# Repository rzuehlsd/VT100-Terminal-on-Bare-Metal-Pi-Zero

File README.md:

# PiVT100 Terminal - Enhanced Edition

A VT100 terminal emulator for Raspberry Pi Zero, forked and refactored from PiGFX by Filippo Bergamasco, now rebranded as PiVT100 and enhanced for use with a custom 60% VT100 replica case and adapter board.

## Motivation

Main motivation was that I wanted a terminal emulation for my VT100 replica. Emulation should start within seconds, so a bare metal implementation on a Pi Zero seems to be the way to go. I found the PiGFX implementation by Filippo Bergamasco and used that as a starting point for my modifications. 

Below you see the original VT100 terminal (the color has turned to yellow over the years) and my 60% replica.

If you want a 100% VT100 terminal emulation please go for the VT100 simulation from Lars Brinkhoff (https://github.com/larsbrinkhoff/terminal-simulator)). He simulates the VT100 hardware with original ROMs on a Raspberry Pi. 

## Requirements

My list of requirements was rather short:
- support of VT100 ANSI control sequences, at least of the most important ones
- simulation of a VT100 font and possibly other alternative fonts
- support white on black, amber on black and green on black as terminal font colors
- include simulation of keyclick and bell sound
- configurable via config file at boot and with setup dialog
- design of an adapter board to provide power (Pi and display), RS232 and custom Mini DIN6 connector for UART host connections
- dynamically switch Rx<>Tx to simulate null modem cable
- 8'' display with at least 800x640 pixel resolution (gives about 80x32 chars with VT100 font)
- provide 5VDC power for connected SBCs, like MBC2-Z80

## What's Different from Original PiGFX

The original PiGFX codebase by Filippo Bergamasco has been reduced to the pure VT100 terminal functionality, fully refactored and renamed as PiVT100. Major changes include:

- Removal of graphics, sprites, palette, and font loading features not relevant to VT100 emulation
- Addition of features for VT100 replica hardware integration (switching Rx/Tx, bell, RS232, custom DIN6 connector)
- Improved configuration system and setup dialog
- Consistent naming: main binary is now `pivt100.elf`, config file is `pivt100.txt`, font tools and scripts updated to PiVT100 naming

### Hardware Integration

- **Custom Adapter Board**: PCB design for Raspberry Pi Zero integration into VT100 case
- **Modified Back Cover**: 3D printable back plate designed for 60% VT100 replica case
- **Optimized Pin Layout**: Connector placement adapted for compact VT100 housing

### Software Enhancements

- **Improved Configuration System**: Enhanced `pivt100.txt` file parsing with better error handling
- **Setup Dialog**: Interactive configuration menu accessible via Print Screen key
- **Font Registry**: Multiple built-in fonts with dynamic switching capability
- **Enhanced Keyboard Support**: Better PS/2 keyboard compatibility and layout options
- **Audio Features**: PWM-based bell sound and optional key click feedback
- **Debug System**: Improved logging with configurable verbosity levels

### Configuration Features

- **Runtime Configuration**: Live settings changes through setup dialog
- **Extended Options**: Additional UART, keyboard, and display settings
- **Rx-Tx Switching**: dynamic switching of Tx <> Rx to simulate null modem cable
- **Safe Defaults**: Fallback configuration when SD card config unavailable
- **Layout Support**: Multiple keyboard layouts (US, UK, DE, etc.)

The following picture shows the setup dialog:

<div align="center">
  
</div>

## Hardware Components

### Adapter Board

The custom PCB provides:

- 5VDC / 2A switching power supply for Pi and display
- Raspberry Pi Zero mounting and connections
- PS/2 keyboard connector
- RS232 DB9 connector to interface with host
- Compact form factor for VT100 case integration

Below you see the schematic of the adapter board. The KiCad project is located in directory hardware.

<div align="center">
  
</div>

The following picture shows the prototype of the adapter board still with linear voltage regulator. Final version will hold a switching buck regulator to reduce heat.

<div align="center">
  
</div>

The cable on top of the picture going to the Pi Zero connects the D+/D- pins of the USB connector at the back to two testpoints on the Pi. This allows the usage of a standard USB keyboard to be connected to the Pi Zero without additional adapter. For more details please see https://maker-tutorials.com/raspberry-pi-zero-mit-usb-buchse-typ-a-erweitern-anloeten/.

As it's very hard to find a real RS232 null modem cable, the signal relay (blue) is used to switch the Rx and Tx lines to simulate a null modem cable, if required.
The resistors between Pi Zero and relay are used to level shift the RxD signal (only signal that goes into the Pi) to voltage levels below 3.3V.
The connectors on the back besides the USB-A are a Mini DIN6 connector (for a custom connection to an MBC2-Z80), an RS232 connector module and a 5.5mm power connector.

More information is given in directory hardware.

### Modified Back Cover

The 3D printable back plate features:

- Mounting points for Raspberry Pi Zero adapter board
- Cutouts for power, UART connections and SD card extension cable
- Compatible with 60% VT100 replica cases

This back cover fits into the opening at the back of the VT100 case and has supports to connect the PCB (holes have to be drilled manually to allow for small adjustments). There is also a support to hold the SD card extension to allow changing the SD card at the back of the case. The other openings fit the connectors on the adapter board and allow mounting of a small ON/OFF switch.

<div align="center">
  
</div>

## Quick Setup

### Hardware Assembly

1. Populate the adapter board starting with the smallest components
2. Check installed submodules (e.g. power supply, connectors, etc.)
3. Install Raspberry Pi Zero on adapter board
4. Mount assembly in VT100 case with modified back cover
5. Connect PS/2 keyboard to adapter board
6. Connect power supply

## Assembly of VT100 replica case

The case was printed on a Bamboo Lab P1S printer using the STL-files provided by megardi. I discovered that the different parts which have to be glued together did not always fit very well. So be prepared to use a lot of filler and do a lot of sanding. It took some time but in the end the result was quite good. I used a special filler for plastics to prepare for the final painting. I discovered that the original color of the VT100 was "oyster white" and by comparing a RAL color table with a picture of the inside of a real VT100 I found that RAL 1013 fits very well.

Here are some pictures of the assembly process:

<div align="center">

</div>

I used a simple 8'' display from Aliexpress with 1024x768 pixels. The display had no brightness regulation (neither per HDMI nor external). For the future I would recommend using a controller with brightness control, if possible through software.

In the pictures above I used the resolution 800x640 pixel. With 1024x768 the first 2 characters are covered by the screen bezel. 

To connect the display to the Pi Zero I used a flexible adapter cable miniHDMI to miniHDMI (C1-C1). I also installed an SD Card extension cable for easy access to the SD card slot at the back of the case.

Display:        https://de.aliexpress.com/item/1005004162403387.html?spm=a2g0o.order_list.order_list_main.64.759e5c5fCtHg3D&gatewayAdapt=glo2deu
Cable:          https://de.aliexpress.com/item/1005008622570470.html?spm=a2g0o.order_list.order_list_main.59.7f095c5f7ZEnkL&gatewayAdapt=glo2deu
SD Card Extension:  https://de.aliexpress.com/item/4001200431510.html?spm=a2g0o.order_list.order_list_main.87.759e5c5fCtHg3D&gatewayAdapt=glo2deu

### Software Installation

1. Format SD card as FAT32
2. Copy `bootcode.bin`, `start.elf`, `kernel.img` and `pivt100.txt` to SD card root
3. Insert SD card and power on
4. Connect UART at 115200 baud for terminal access
5. Adjust terminal settings via setup dialog to your needs

### Configuration

- **Interactive Setup**: Press Print Screen key when the keyboard is connected
- **File Configuration**: Edit `pivt100.txt` on SD card for persistent settings
- **Default Settings**: System works out-of-box with reasonable defaults

## Basic Configuration (`pivt100.txt`)

```ini
# Display Settings
displayWidth = 1024
displayHeight = 768
fontSelection = 2
foregroundColor = 10
backgroundColor = 0

# UART Settings
baudrate = 115200
switchRxTx = 0

# Keyboard Settings
keyboardLayout = us
useUsbKeyboard = 1
keyboardAutorepeat = 1

# Audio Settings
soundLevel = 50
keyClick = 1
```

## Building from Source

```bash
# Build for Raspberry Pi Zero
make RPI=1

# Clean build
make clean
```

## Known Issues

### Display Frame Coverage

- **1024x768 Resolution**: First two characters may be covered by screen bezel
- **Workaround**: Avoid critical text in leftmost positions
- **Future Fix**: Logical screen offset implementation planned

## Hardware Files

- **PCB Design**: Located in `/hardware` directory (KiCad format)
- **3D Models**: OpenSCAD files for back cover modifications in `/OpenScad`
- **Assembly Guide**: See `/doc` for detailed assembly instructions

## Project History

This project is a fork and full refactor of [PiGFX](https://github.com/fbergama/pigfx) by Filippo Bergamasco. All code, configuration, and documentation have been updated to use the PiVT100 name and structure. The original project provided the core VT100 terminal emulation and graphics capabilities.

VT100 replica in 60% size was designed by megardi (https://www.instructables.com/23-Scale-VT100-Terminal-Reproduction/).

## License

Copyright (C) 2014-2020 Filippo Bergamasco (Original PiGFX)
Copyright (C) 2025 Ralf Zühlsdorff (PiVT100 Edition)

Licensed under the MIT License - see LICENSE file for details.

## Contributing

Contributions welcome for:

- Hardware design improvements
- Software feature enhancements  
- Documentation updates
- Testing on different Pi models

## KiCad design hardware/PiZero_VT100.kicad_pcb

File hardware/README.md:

# Carrier Board for Pi Zero VT100 Terminal
<div align="center">
RZ 9/2015
</br>
</br>
</div>

This project designs and builds a carrier board for the Raspberry Pi Zero that, together with the pigfx_V20 software, enables a bare‑metal implementation of a VT100 terminal.

The software features are described in the directory PIGFX_20, including the enhancements over the original version. This software version extends the PiGFX project by Filippo Bergamasco.

The carrier board can be mounted directly in the rear panel of a terminal enclosure and provides the following components:
- 5 VDC / 2 A power supply (input 7–9 V DC or AC / 2 A wall adapter)
- RS‑232 interface to the host computer
- Alternative host interface via Mini‑DIN‑6 connector and 4‑pin header
- USB‑A connector for a wired USB keyboard
- Switch (relay) to swap RxD and TxD
- 800 Hz buzzer (optional)

The Pi Zero GPIO pins are not 5 V tolerant. Therefore, all incoming signals (here: RxD only) must be level‑shifted from 5 V to 3.3 V. Outgoing signals are 5 V‑level compatible for typical systems.

The RxD level shifting is implemented with a resistor divider: 820 Ω and 1.5 kΩ. No issues have been observed even at 115200 baud.

The updated version was prototyped on the old PCB. The 74HC5040 was desoldered and the RxD signal was routed to the Pi through the resistor divider. All other signals were wired directly to the Pi Zero with jumpers.

Testing also showed that the 7805 linear regulator needs a small heatsink for stable operation. On the old board, a small heatsink was provisionally installed for testing. With the heatsink, the 7805 ran stably and supplied power not only to the Pi Zero but also to the MSBC2‑Z80 running CP/M. 

In the final version, the LCD display must also be supplied from the 5 V rail with about 1 A. Therefore, the 5 V supply must provide at least 2 A and use a larger heatsink with about 6 K/W thermal resistance. Therefore the 7805 was replaced by a LM350 regulator, which can provided up to 3A with proper heatsink.

All changes have been reflected in the schematic and layout.

An adapter for the MBC2‑Z80 to connect the Z80 via the Mini‑DIN‑8 connector is described in the sub‑project “Z80‑SBC_Adapter”.

Board revisions:
- [x] Barrel jack for 9 V DC / AC input
- [x] Replace regulator with LM350
- [x] Check heatsink and install a larger one if needed
- [x] LED indicator On/Off
- [x] Contacts for power switch
- [x] RxD <> TxD swap via relay, switchable by Pi GPIO pin
- [x] USB‑A socket for keyboard connection
- [x] Mini‑DIN‑6 socket for direct MBC2 connection with power
- [x] RS‑232 DB9 connector
- [x] Internal header for direct MBC2 connection inside the terminal enclosure
- [x] PCB cut‑out for the USB plug (very short pins)
- [x] Buzzer / speaker circuit added
    - [x] Pads for piezo buzzer, 12.5 mm diameter, 5 mm pitch
- [x] Schematic revised for external fabrication

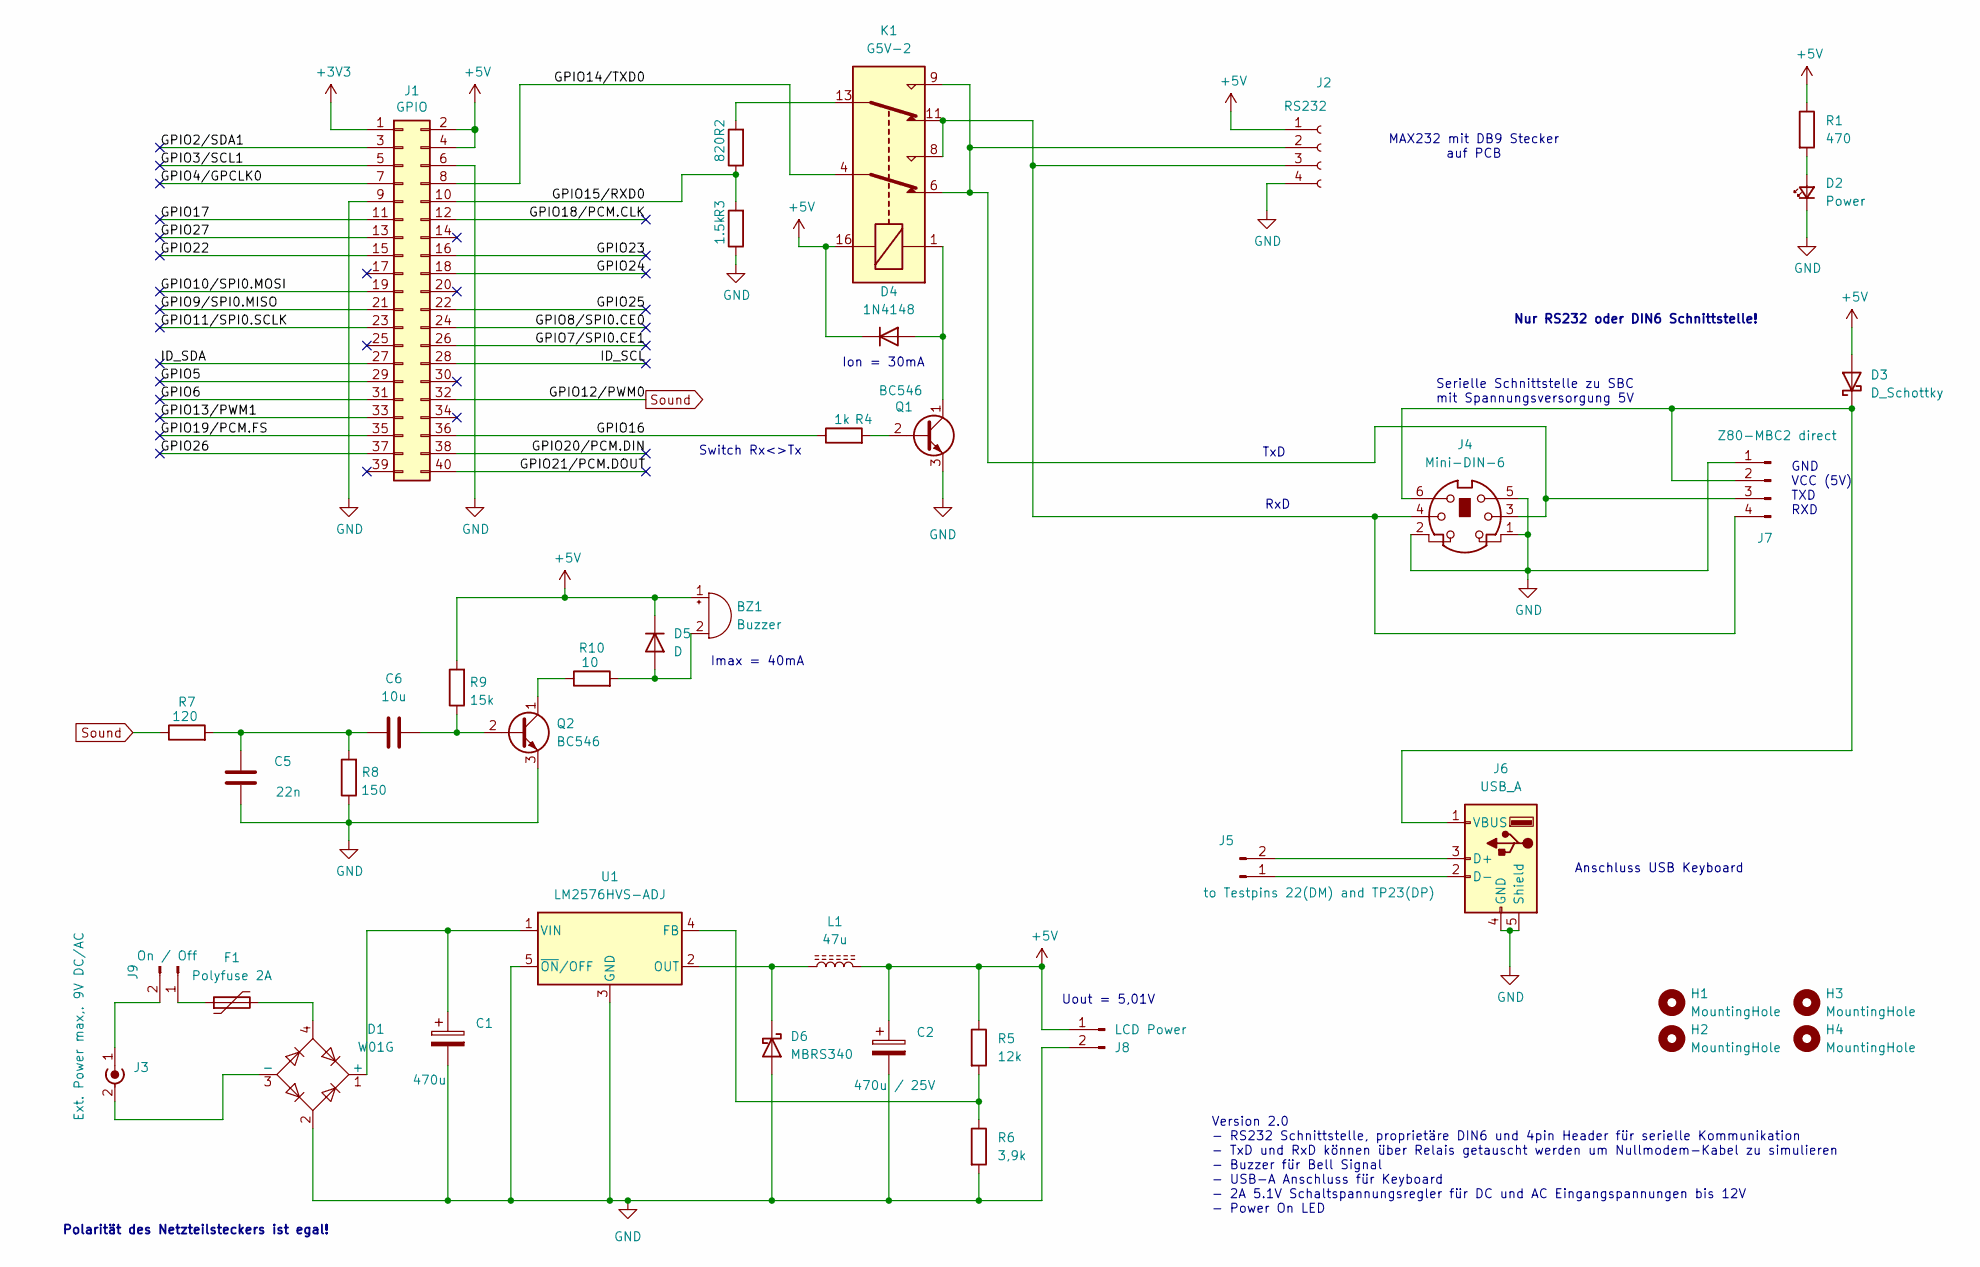
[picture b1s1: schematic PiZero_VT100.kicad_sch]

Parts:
BZ1: Buzzer; MagneticBuzzer_ProSignal_ABI-009-RC
C1: 470u; CP_Elec_10x10
C2: 470u / 25V; CP_Elec_10x10
C5: 22n; C_Rect_L7.0mm_W4.5mm_P5.00mm
C6: 10u; C_Rect_L9.0mm_W2.6mm_P7.50mm_MKT
D1: W01G; Diode_Bridge_Round_D9.8mm
D2: Power; LED_D3.0mm
D3: D_Schottky; D_DO-15_P12.70mm_Horizontal
D4: 1N4148; D_A-405_P10.16mm_Horizontal
D5: D; D_A-405_P10.16mm_Horizontal
D6: MBRS340; D_SMC
F1: Polyfuse 2A; Fuse_Littelfuse-LVR200
H1, H2, H3, H4: MountingHole; MountingHole_3.2mm_M3
J1: GPIO; PinSocket_2x20_P2.54mm_Vertical
J2: RS232; PinSocket_1x04_P2.54mm_Vertical
J3: Ext. Power max,. 9V DC/AC; BarrelJack_GCT_DCJ200-10-A_Horizontal
J4: Mini-DIN-6; J_Mini-DIN-6
J5: to Testpins 22(DM) and TP23(DP); PinHeader_1x02_P2.54mm_Vertical
J6: USB_A; USB_A_Stewart_SS-52100-001_Horizontal
J7: Z80-MBC2 direct; PinHeader_1x04_P2.54mm_Vertical
J8: LCD Power; PinHeader_1x02_P2.54mm_Vertical
J9: On / Off; PinHeader_1x02_P2.54mm_Vertical
K1: G5V-2; Relay_DPDT_Omron_G5V-2
L1: 47u; L_Fastron_PISN
Q1, Q2: BC546; TO-92_Wide
R1: 470; R_Axial_DIN0207_L6.3mm_D2.5mm_P10.16mm_Horizontal
R2: 820; R_Axial_DIN0207_L6.3mm_D2.5mm_P10.16mm_Horizontal
R3: 1.5k; R_Axial_DIN0207_L6.3mm_D2.5mm_P10.16mm_Horizontal
R4: 1k; R_Axial_DIN0207_L6.3mm_D2.5mm_P10.16mm_Horizontal
R5: 12k; R_1206_3216Metric_Pad1.30x1.75mm_HandSolder
R6: 3,9k; R_1206_3216Metric_Pad1.30x1.75mm_HandSolder
R7: 120; R_Axial_DIN0207_L6.3mm_D2.5mm_P10.16mm_Horizontal
R8: 150; R_Axial_DIN0207_L6.3mm_D2.5mm_P10.16mm_Horizontal
R9: 15k; R_Axial_DIN0207_L6.3mm_D2.5mm_P10.16mm_Horizontal
R10: 10; R_Axial_DIN0207_L6.3mm_D2.5mm_P10.16mm_Horizontal
U1: LM2576HVS-ADJ; TO-263-5_TabPin3

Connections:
+3V3: J1.1
+5V: BZ1.1 (+), C2.1, D3.2 (A), D4.1 (K), D5.1 (K), J1.2, J1.4, J2.1, J8.1, K1.16, L1.2, R1.1, R5.1, R9.2
/GPIO2/SDA1: J1.3
/GPIO3/SCL1: J1.5
/GPIO4/GPCLK0: J1.7
/GPIO5: J1.29
/GPIO6: J1.31
/GPIO7/SPI0.CE1: J1.26
/GPIO8/SPI0.CE0: J1.24
/GPIO9/SPI0.MISO: J1.21
/GPIO10/SPI0.MOSI: J1.19
/GPIO11/SPI0.SCLK: J1.23
/GPIO13/PWM1: J1.33
/GPIO14/TXD0: J1.8, K1.4
/GPIO15/RXD0: J1.10, R2.1, R3.2
/GPIO16: J1.36, R4.1
/GPIO17: J1.11
/GPIO18/PCM.CLK: J1.12
/GPIO19/PCM.FS: J1.35
/GPIO20/PCM.DIN: J1.38
/GPIO21/PCM.DOUT: J1.40
/GPIO22: J1.15
/GPIO23: J1.16
/GPIO24: J1.18
/GPIO25: J1.22
/GPIO26: J1.37
/GPIO27: J1.13
/ID_SCL: J1.28
/ID_SDA: J1.27
GND: C1.2, C2.2, C5.2, D1.2, D2.1 (K), D6.2 (A), J1.6, J1.9, J2.4, J4.1, J4.2, J4.5, J6.4 (GND), J6.5 (Shield), J7.1, J8.2, Q1.3 (E), Q2.3 (E), R3.1, R6.2, R8.1, U1.3 (GND), U1.5 (~ON/OFF)
unnamed: BZ1.2 (-), D5.2 (A), R10.2
unnamed: C5.1, C6.1, R7.2, R8.2
unnamed: C1.1, D1.1 (+), U1.1 (VIN)
unnamed: D1.3 (-), J3.2 (Ext)
unnamed: D1.4, F1.2
unnamed: D2.2 (A), R1.2
unnamed: D3.1 (K), J4.6, J6.1 (VBUS), J7.2
unnamed: D4.2 (A), K1.1, Q1.1 (C)
unnamed: D6.1 (K), L1.1, U1.2 (OUT)
unnamed: J2.2, J4.3, J7.3, K1.6, K1.9
unnamed: J2.3, J4.4, J7.4, K1.8, K1.11
unnamed: J3.1 (In), J9.2
unnamed: J5.1, J6.2 (D-)
unnamed: J5.2, J6.3 (D+)
unnamed: F1.1, J9.1
unnamed: K1.13, R2.2
unnamed: Q1.2 (B), R4.2
unnamed: C6.2, Q2.2 (B), R9.1
unnamed: Q2.1 (C), R10.1
unnamed: R5.2, R6.1, U1.4 (FB)
Sound: J1.32, R7.1

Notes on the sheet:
Imax = 40mA
TxD
RxD
Version 2.0 - RS232 Schnittstelle, proprietäre DIN6 und 4pin Header für serielle Kommunikation - TxD und RxD können über Relais getauscht werden um Nullmodem-Kabel zu simulieren - Buzzer für Bell Signal - USB-A Anschluss für Keyboard - 2A 5.1V Schaltspannungsregler für DC und AC Eingangspannungen b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
Ion = 30mA
MAX232 mit DB9 Stecker auf PCB
Anschluss USB Keyboard
Nur RS232 oder DIN6 Schnittstelle!
Serielle Schnittstelle zu SBC mit Spannungsversorgung 5V
Switch Rx<>Tx
GND VCC (5V) TXD RXD
Uout = 5,01V
Polarität des Netzteilsteckers ist egal!

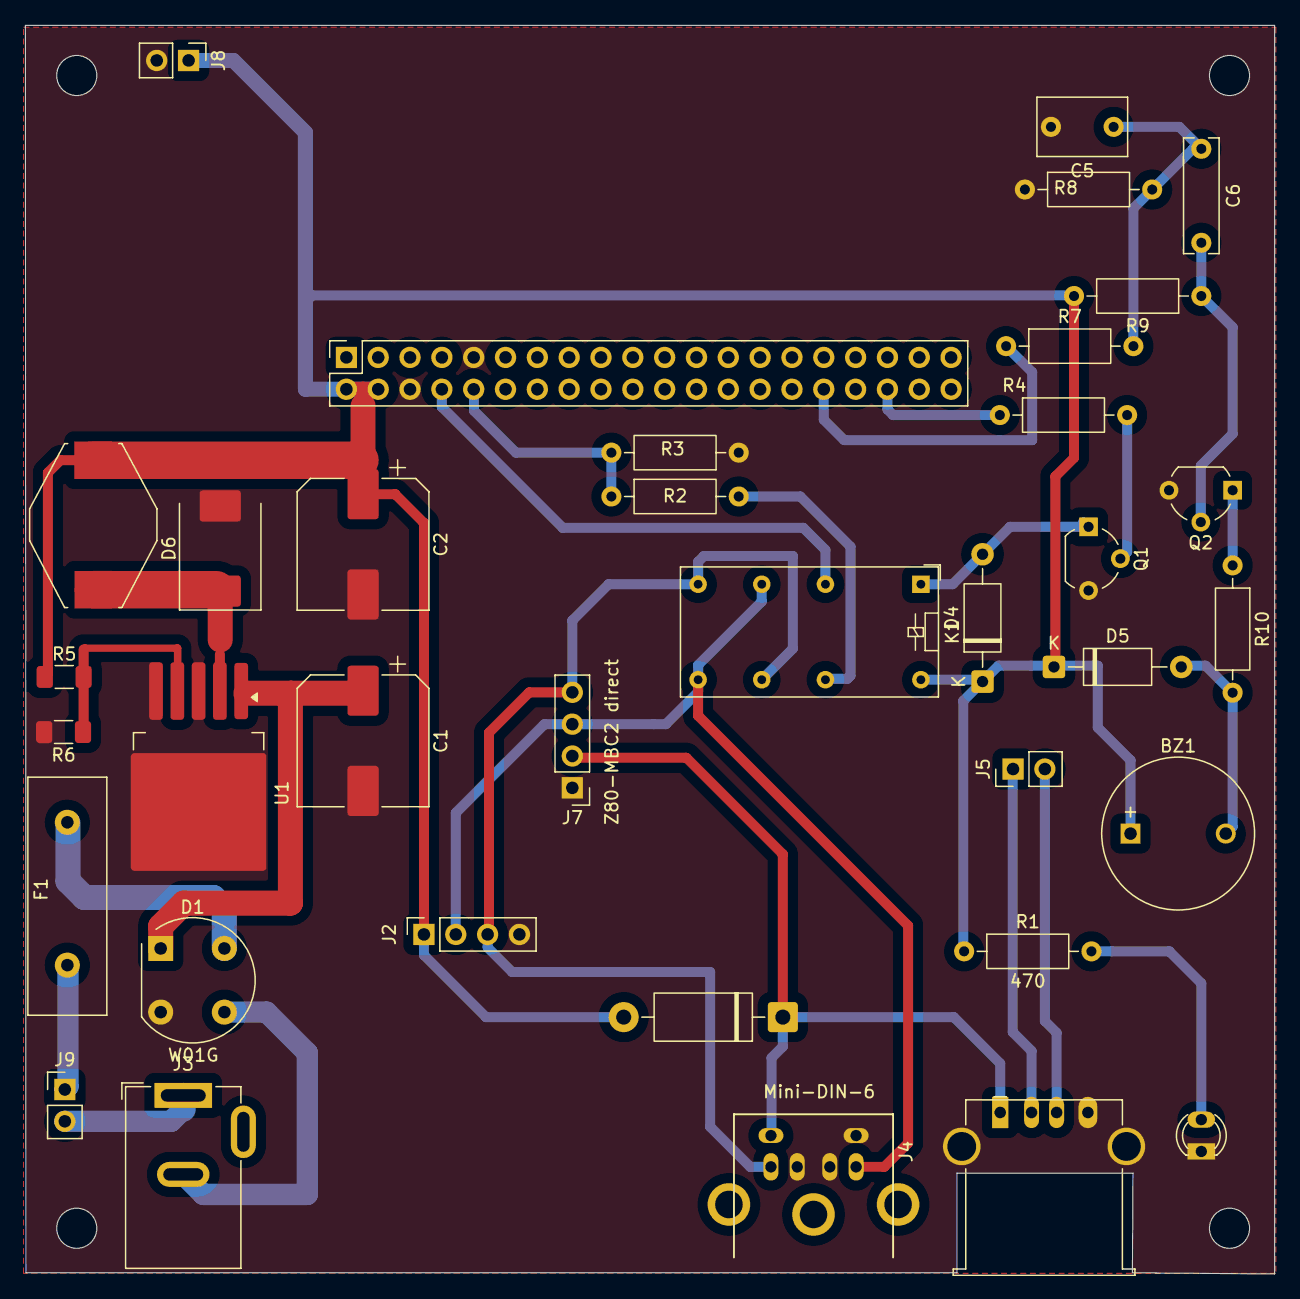
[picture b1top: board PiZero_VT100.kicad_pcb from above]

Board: 2 copper layers, 99.7 x 99.6 mm, 40 parts (0 on the bottom side), 26 nets.

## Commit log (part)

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2025-08-13 uspi wurde von git repository gecloned in Directory uspi und lässt sich wie im entsprechenden Readme beschrieben kompilieren. Wechsel zurück in das pigfx Verzeichnis und aufruf von ./makeall erzeuigt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
2025-08-13 Build files updated to compile for Pi zero. Different architectures used for build cause undefined instruction error and halt at boot. System compiles and boots now without problem.
2025-08-14 Setup dialog teilweise implementiert. - Setzen der BAudrate (test noch offen) - Setzen des keyboard layouts (verifiziert)
2025-08-14 changing fore and background color works
2025-08-14 Save working setup mode with 4 features: baudrate, keyboard, fg/bg colors
    - Complete setup mode with Print key activation
    - Baudrate selection (10 options: 300-115200)
    - Keyboard layout selection (7 layouts: us,uk,it,fr,es,de,sg)
    - Foreground color selection (16 colors with preview)
    - Background color selection (16 colors with preview)
    - Screen buffer management and color preservation
2025-08-15 Add Spleen font family integration and enhanced setup mode
    Features:
    - Convert and integrate complete Spleen font family (6x12, 8x16, 12x24, 16x32, 32x64)
    - Add bdf2pigfx converter tool for BDF to PiGFX binary format conversion
    - Enhance setup mode to 5 features: Baudrate, Keyboard, Colors, Font selection
    - Add precise font type detection to distinguish between fonts with identical dimensions
    - Improve setup dialog layout with wider box and better font name display
2025-08-15 Complete font management system and setup dialog implementation
    This commit represents a successful milestone in implementing font size changes
    in the setup dialog with a complete redesign of the font system.
    Major Components:
    - Generic font registry system (font_registry.c/h) replacing hardcoded approach
    - Complete Spleen font family integration (6x12, 8x16, 12x24, 16x32, 32x64)
    - Fixed BDF to PiGFX converter (bdf2pigfx.cpp) that was corrupting font files
2025-08-15 Upgrade framebuffer resolution to 1024x768
    - Changed initialize_framebuffer from 640x480 to 1024x768 in pigfx.c
    - Provides ~60% more screen real estate (128x48 vs 80x30 characters)
    - Setup dialog automatically centers in larger display
    - All fonts scale beautifully with increased resolution
    - Terminal dimensions recalculate dynamically
    - Memory usage increases to ~786KB per framebuffer (well within Pi limits)
2025-08-16 Implement comprehensive two-stage configuration system with resolution selection
    MAJOR FEATURES IMPLEMENTED:
    - Two-stage configuration system for stable boot process
    - Dynamic resolution switching (640x480 ↔ 1024x768)
    - Enhanced setup dialog with 6 configuration options
    - Comprehensive configuration documentation in pigfx.txt
    - Robust font registry integration with error handling
2025-08-16 feat: PiGFX Enhanced Edition v2.0.0 - Unified Build System & Two-Stage Configuration
    Major Features:
    ✅ Two-Stage Configuration System
    - Safe boot config applied before 'Waiting for UART..' message
    - User config applied after UART initialization for proper timing
    - Fixes font/color persistence and configuration timing issues
    ✅ Unified Build System
2025-08-16 feat: Add uspi debug filtering and auto-clone functionality
    Features:
    - Modified LogWrite in ee_printf.c to only output [NOTICE ] level messages
    - Filters out uspi ERROR, WARNING, and DEBUG messages to reduce spam
    - Added automatic uspi repository cloning if directory is missing
    - Added cleanall target to remove uspi directory for fresh clone
    - Added comprehensive help target with usage instructions
2025-08-16 feat: Implement simplified bitmap-based debug severity system
    - Add debug_levels.h with bitmap severity levels (ERROR, WARNING, NOTICE, DEBUG)
    - Replace compile-time DEBUG_SEVERITY with runtime g_debug_severity variable
    - Add SetDebugSeverity() and GetDebugSeverity() functions for runtime control
    - Implement simplified logging macros: LogError(), LogWarning(), LogNotice(), LogDebug()
    - Automatic __FILE__ and __LINE__ inclusion for ERROR and DEBUG levels only
    - Remove redundant severity parameters from macro calls
2025-08-16 feat: Complete logging system modernization with USPI compatibility
    Major improvements:
    - Migrate pigfx.c to use new bitmap-based debug system
    - Replace compile-time SYSTEM_DEBUG with runtime debug control
    - Add enhanced logging macros with automatic color management
    - Fix USPI compatibility: convert old severity values (1,2,3,4) to bitmap format
    - Eliminate '[ ?? ]' output from USPI messages
2025-08-17 Refactor banner display and complete logging system overhaul
    - Refactored banner display code into reusable display_system_banner() function
    - Eliminated code duplication between initial startup and resolution change scenarios
    - Enhanced banner formatting with proper line clearing and color management
    - Updated copyright notice to include all contributors (2016-2025)
    Logging System Improvements:
    - Fixed debug verbosity system - now properly responds to verbosity=2 setting
2025-08-17 Add comprehensive development summary documentation
    - Created ENHANCEMENT_SUMMARY.md with complete overview of all improvements
    - Documents logging system transformation from basic printf to enterprise-grade
    - Details banner refactoring and code deduplication achievements
    - Comprehensive technical improvements and critical fixes documentation
    - User experience enhancements and code quality improvements
    - Metrics and impact analysis of all changes
2025-08-17 Update enhancement summary: add Spleen font support, BGF converter, and USPi build automation
    - Documented Spleen font integration and runtime selection
    - Added BGF converter utility for custom bitmap font import
    - Noted automatic USPi git clone and build integration in build system
    - Ensured summary covers all major improvements since commit 6cc6ed1
    This keeps the documentation fully up to date with all recent enhancements.
2025-08-17 intermediate documentation version Functional problems: - Autorepeat somtimes runs wild
    Other:
    - Documentation has to bestreamlined and condensed to just reflect changes implemented and not old features
    Should state that this is a forl of the roiginal work from Bergama
    Prepare documentation for public commit as fork
2025-08-18 auto repeat function implemented at one place in keyboard.c for ps/2 and usb keyboards. Seems to work but needs further testing
2025-08-18 Fix keyboard autorepeat: correct timer conversion, set default to 500ms delay and 10 chars/sec repeat rate, disable debug output
2025-08-18 Keyboard repeat: Use config values directly for repeat delay and frequency. Clean up timing code in main loop. Now repeat rate and delay are fully controlled by pigfx.txt settings. Visible repeat rat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
2025-08-19 Cursor rendering: swap fg/bg color for 8bpp framebuffer (if pixel matches fg, set to bg and vice versa, using 8-bit values)
2025-08-19 Add cursorBlink config: cursor blinking can now be enabled/disabled via pigfx.txt (applies at startup)
2025-08-19 Fix cursor blinking artifacts, ensure clean transition between blinking and static cursor, and enable runtime toggle via setup dialog
2025-08-19 Add keyboard repeat delay and rate to setup dialog with runtime update support (200-1000ms, 10-50Hz)
2025-08-19 Setup dialog: Add Auto Repeat On/Off config, immediate apply of all settings, and improved UI. All setup options now function as expected.
2025-08-19 Remove showRC2014Logo: eliminate config flag, all code, and documentation references. Cleaned up all related logic and config files.
2025-09-04 Fix font descender/cursor logic, VT220 font support, and various rendering improvements
2025-09-05 VT220 font still not correctly rendered. j,p,q etc. have problems.
2025-09-05 Änderung der bdf Konvertierung durch hochschieben des Startpunkts der Glyphe iin Font Box hat keine Auswirkung auf Darstellung. Zeichen mit unterlängen werden nicht korrekt angezeigt. Die Darstellung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
2025-10-02 Fontregistry eingebaut und getestet - setzen der Font klappt aber VT220 12x24 ist korrumpiert - VT100 10x20 sieht sehr gut aus - die Screen Resolution ändert sich nicht - Auflösung 800x640 fehlt - be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
2025-10-02 - Screen Resolution ändert sich und übernimmt die aktuellen Einstellungen - Auflösung 800x640 hinzugefügt
2025-10-03 kleine Änderungen an setup.cfont make file überarbeitet - aus binary font files in bin dir wird automatisch ein binary_assets.s file sowie ein buildin_fonts.inc file erzeugt um die fonts automatisch 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
2025-10-03 generate bin files for VT220 larger fonts from scratch with python script but still chars are distorted on screen. Not quite clear what is going on here. Does not seem to be an issue with the font bu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
2025-10-04 Soweit ok , aber Probleme beim Setzen der Konfiguration vom File File wird gelesen, aber die richtige Konfiguration wird nicht bei applyConfig gesetzt. Default Konfiguration wird teilweise gesetzt - 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
2025-10-04 Fehler des unvollständigen Umsetzens der Konfiguration gefunden! In allen Debug und Log Messages waren explizite Farbsetzungen drin, die dann immer auf eine feste Vordergrundfarbe (hellgrau) zurückge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
2025-10-06 Changed Makefile to also handle the buildin_fonts.inc file Now we have 4 fonts available Screen clearing after font change ok
2025-10-09 neues Setup Attribut CRLF eingefügt und kleinere Fehler im Setupdialog behoben
2025-10-09 Implementierung von Rx Tx Switching ist sowiet ok - Ansteuerung des Relais über GPIO16 klappt - Setup Dialog und Config sind angepasst und ok - Kleiner Fehler: Wenn man fon Off nach On schaltet und d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
2025-10-09 Implementation des 800Hz 250ms Bell Tons erfolgreich mit Software PWM realisiert und an Lautsprecher getestet
2025-10-09 Erste einsetzbare Version! - Buzzer auf 785Hz - Setup und Konfiguration von sound level und flag replace Lf wit Cr
2025-10-10 added hardware directory and KiCAD files for adapter board and updated the readme
2025-10-10 Added pictures to readme
2025-10-10 removed files not required
2025-10-10 removed additional files not required
2025-10-10 clean up
2025-10-10 small changes
2025-10-10 corrections to readme
2025-10-12 Additions to readme
2025-10-12 small changes, typos
2025-10-12 support for sprites removed from code and repository
2025-10-12 Sprite support completely removed from project
2025-10-12 Analyzing VT100 support and extension
2025-10-12 Readme has now a section about VT100 compatibility
2025-10-13 OpenScad model für rückseitige Monatgeöffnung
2025-10-13 small additions to readme
2025-10-14 small changes to readme
2025-10-23 Bell sound with buzzer works and also key click, which is configurable in setup dialog and configuration file. There is some interferebce when debug level is 2 as debug output interrupts pwm generati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
2025-10-24 setup dialog in current fg and bg color Needs some refactoring!
2025-10-24 Setup Dialog refactored, uses only selected fg and bg Color selection reduced to black, white, green and yellow
2025-10-24 removed sprite handling, bitmap and pallette loading functions
2025-10-24 Readme aktualisiert
2025-10-24 Adapterplatine V2.0 mit Schaltregler. da Linearregler zu hohe Wärmeentwicklung hat
2025-10-25 Änderungen in Schematic
2025-10-25 PCB Adapterboard geändert
2025-10-25 Modified Readme
2025-10-25 Modifikation of Readme, addition of pictures
2025-10-25 Erweitertes Readme
2025-10-25 small modification Readme
2025-10-25 Remove drawing modes XOR and Transparent and related function
2025-10-25 removed all graphics related functions in gfx and solved compiler warnings
2025-10-25 bitmap and palette functions and datastructures removed
2025-10-25 Alle PiGFX Extensions have been removed. Lit of implemented VT100 features has been created and holds a section of missing functionality.
2025-10-27 kleine Änderungen am Setup Dialog
2025-10-27 Readme updated
2025-10-27 added correct link to L. Brinkhoff
2025-10-27 Updates to Readme
2025-10-27 Update to readme
2025-10-27 spelling corrections in readme
